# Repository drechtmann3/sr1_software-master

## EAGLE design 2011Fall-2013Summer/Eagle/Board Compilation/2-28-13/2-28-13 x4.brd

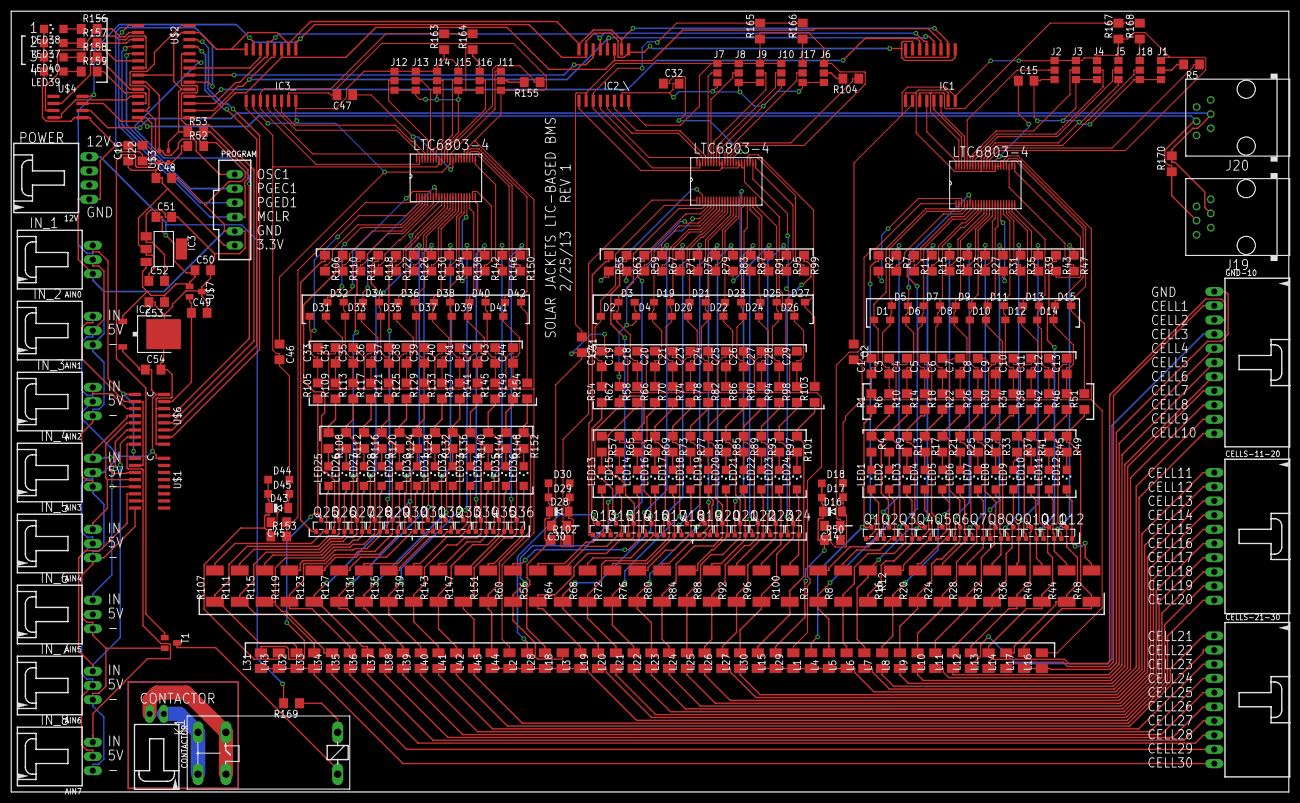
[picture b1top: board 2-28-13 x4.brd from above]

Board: 2 copper layers, 228.6 x 139.7 mm, 437 parts (0 on the bottom side), 350 nets.

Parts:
12V: C-GRID-04-70553; 70553-04
AIN0, AIN1, AIN2, AIN3, AIN4, AIN5, AIN6, AIN7: C-GRID-03-70553; 70553-03
C1, C3, C4, C5, C6, C7, C8, C9, C10, C11, C12, C13, C14, C17, C18, C19, C20, C21, C23, C24, C25, C26, C27, C28, C29, C30, C33, C34, C35, C36, C37, C38, C39, C40, C41, C42, C43, C44, C45: 100nF 100V; C1206
C2, C15, C22, C31, C32, C46, C47, C50, C51, C53: 1uF; C1206
C16, C48, C49, C52, C54: .1uF; C1206
CELLS-11-20, CELLS-21-30: C-GRID-10-70553; 70553-10
CONTACTOR: C-GRID-02-70553; 70553-02
D1, D2, D3, D4, D5, D6, D7, D8, D9, D10, D11, D12, D13, D14, D15, D19, D20, D21, D22, D23, D24, D25, D26, D27, D31, D32, D33, D34, D35, D36, D37, D38, D39, D40, D41, D42: PDZ7.5B; SOD323-W
D16, D28, D43: ZMM5265B-7; MINIMELF
D17, D18, D29, D30, D44, D45: BAT46W; SOD123
GND-10: C-GRID-11-70553; 70553-11
IC1, IC2_\, IC3_: ADUM1401; SO16W
IC2: 7805DT; TO252
IC3: REG1117; SOT223
J1: TOS_LTC1; A0R-JMP
J2: A3_LTC1; A0R-JMP
J3: A2_LTC1; A0R-JMP
J4: A1_LTC1; A0R-JMP
J5: A0_LTC1; A0R-JMP
J6: TOS_LTC2; A0R-JMP
J7: A3_LTC2; A0R-JMP
J8: A2_LTC2; A0R-JMP
J9: A1_LTC2; A0R-JMP
J10: A0_LTC2; A0R-JMP
J11: TOS_LTC3; A0R-JMP
J12: A3_LTC3; A0R-JMP
J13: A2_LTC3; A0R-JMP
J14: A1_LTC3; A0R-JMP
J15: A0_LTC3; A0R-JMP
J16: WDTB_LTC3; A0R-JMP
J17: WDTB_LTC2; A0R-JMP
J18: WDTB_LTC1; A0R-JMP
J19, J20: RJ11-2L-B; RJ11-NO_SHIELD
K1: G2REA
L1, L2, L3, L4, L5, L6, L7, L8, L9, L10, L11, L12, L13, L14, L15, L16, L17, L18, L19, L20, L21, L22, L23, L24, L25, L26, L27, L28, L29, L30, L31, L32, L33, L34, L35, L36, L37, L38, L39, L40, L41, L42, L43, L44, L45: IMC1210ER100K; L3225M
LED1, LED2, LED3, LED4, LED5, LED6, LED7, LED8, LED9, LED10, LED11, LED12, LED13, LED14, LED15, LED16, LED17, LED18, LED19, LED20, LED21, LED22, LED23, LED24, LED25, LED26, LED27, LED28, LED29, LED30, LED31, LED32, LED33, LED34, LED35, LED36: BLUE; CHIPLED_1206
LED37, LED40: YELLOW; CHIPLED_1206
LED38: RED; CHIPLED_1206
LED39: GREEN; CHIPLED_1206
LTC1, LTC2, LTC3: LTC6803-4; SSOP44
PROGRAM: C-GRID-06-70543; 70543-06
Q1, Q2, Q3, Q4, Q5, Q6, Q7, Q8, Q9, Q10, Q11, Q12, Q13, Q14, Q15, Q16, Q17, Q18, Q19, Q20, Q21, Q22, Q23, Q24, Q25, Q26, Q27, Q28, Q29, Q30, Q31, Q32, Q33, Q34, Q35, Q36: SI2351DS; MICRO3
R1, R6, R10, R14, R18, R22, R26, R30, R34, R38, R42, R46, R51, R54, R58, R62, R66, R70, R74, R78, R82, R86, R90, R94, R98, R103, R105, R109, R113, R117, R121, R125, R129, R133, R137, R141, R145, R149, R154: 100 1%; R1206
R2, R7, R11, R15, R19, R23, R27, R31, R35, R39, R43, R47, R55, R59, R63, R67, R71, R75, R79, R83, R87, R91, R95, R99, R106, R110, R114, R118, R122, R126, R130, R134, R138, R142, R146, R150: 3.3K; R1206
R3, R8, R12, R16, R20, R24, R28, R32, R36, R40, R44, R48, R56, R60, R64, R68, R72, R76, R80, R84, R88, R92, R96, R100, R107, R111, R115, R119, R123, R127, R131, R135, R139, R143, R147, R151: 33 1W; R2512
R4, R9, R13, R17, R21, R25, R29, R33, R37, R41, R45, R49, R57, R61, R65, R69, R73, R77, R81, R85, R89, R93, R97, R101, R108, R112, R116, R120, R124, R128, R132, R136, R140, R144, R148, R152, R156, R157, R158, R159: 62; R1206
R5, R104, R155, R163, R164, R165, R166, R167, R168: 1M; R1206
R50, R102, R153: 100; R1206
R52: 10k\; R1206
R53: 470; R1206
R169: 1K; R1206
R170: 120; R1206
T1: PMV56XN; SOT23
U$1: SP720APP; SO16
U$2: PIC24HJ128GP-202; SO28W
U$3: ASE
U$4: MAX3440E; SO-08
U$6: MCP-3008; SO16
U$7: MAX6105; SOT23

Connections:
12V: 12V.4, C50.1, C51.1, C53.1, IC2.1, IC3.3, R169.2, U$7.1
+3V3: C16.1, C48.1, C52.1, IC3.2, PROGRAM.6, R52.1, U$2.13, U$2.28, U$3.1, U$3.4
+5V: AIN0.2, AIN1.2, AIN2.2, AIN3.2, AIN4.2, AIN5.2, AIN6.2, AIN7.2, C54.1, IC1.1, IC1.7, IC2.2, IC2_\.1, IC2_\.7, IC3_.1, IC3_.7, U$1.16, U$4.8, U$6.16
AGND: C17.2, C18.2, C19.2, C20.2, C21.2, C23.2, C24.2, C25.2, C26.2, C27.2, C28.2, C29.2, C30.2, C31.2, C32.2, D28.A, D29.A, D30.A, IC2_\.9, IC2_\.15, J6.3, J7.3, J8.3, J9.3, J10.3, J17.3, L29.2, LTC2.P$27, LTC2.P$28, LTC2.P$29, LTC2.P$30, LTC2.P$35, LTC2.P$36
CELL0: GND-10.1, L16.1, L17.1
CELL1: GND-10.2, L14.1
CELL2: GND-10.3, L13.1
CELL3: GND-10.4, L12.1
CELL4: GND-10.5, L11.1
CELL5: GND-10.6, L10.1
CELL6: GND-10.7, L9.1
CELL7: GND-10.8, L8.1
CELL8: GND-10.9, L7.1
CELL9: GND-10.10, L6.1
CELL10: GND-10.11, L1.1, L4.1, L5.1, L15.1, L29.1, L30.1
CELL11: CELLS-11-20.1, L27.1
CELL12: CELLS-11-20.2, L26.1
CELL13: CELLS-11-20.3, L25.1
CELL14: CELLS-11-20.4, L24.1
CELL15: CELLS-11-20.5, L23.1
CELL16: CELLS-11-20.6, L22.1
CELL17: CELLS-11-20.7, L21.1
CELL18: CELLS-11-20.8, L20.1
CELL19: CELLS-11-20.9, L19.1
CELL20: CELLS-11-20.10, L2.1, L3.1, L18.1, L28.1, L44.1, L45.1
CELL21: CELLS-21-30.1, L42.1
CELL22: CELLS-21-30.2, L41.1
CELL23: CELLS-21-30.3, L40.1
CELL24: CELLS-21-30.4, L39.1
CELL25: CELLS-21-30.5, L38.1
CELL26: CELLS-21-30.6, L37.1
CELL27: CELLS-21-30.7, L36.1
CELL28: CELLS-21-30.8, L35.1
CELL29: CELLS-21-30.9, L34.1
CELL30: CELLS-21-30.10, L31.1, L32.1, L33.1, L43.1
GND: C1.2, C2.2, C3.2, C4.2, C5.2, C6.2, C7.2, C8.2, C9.2, C10.2, C11.2, C12.2, C13.2, C14.2, C15.2, D16.A, D17.A, D18.A, IC1.9, IC1.15, J1.3, J2.3, J3.3, J4.3, J5.3, J18.3, L16.2, LTC1.P$27, LTC1.P$28, LTC1.P$29, LTC1.P$30, LTC1.P$35, LTC1.P$36
GNDIO: 12V.1, AIN0.1, AIN1.1, AIN2.1, AIN3.1, AIN4.1, AIN5.1, AIN6.1, AIN7.1, C16.2, C22.2, C48.2, C49.2, C50.2, C51.2, C52.2, C53.2, C54.2, IC1.2, IC1.8, IC2.3, IC2_\.2, IC2_\.8, IC3.1, IC3_.2, IC3_.8, LED37.C, LED38.C, LED39.C, LED40.C, PROGRAM.5, R52.2, R53.1, T1.2, U$1.8, U$2.8, U$2.19, U$2.27, U$3.2, U$4.5, U$6.9, U$6.14, U$7.3
MCLR: PROGRAM.4, R53.2, U$2.1
unnamed: C1.1, D1.C, LTC1.P$2, R1.2
unnamed: L1.2, Q1.3, R1.1
unnamed: LTC1.P$3, R2.2
unnamed: K1.2, T1.3
unnamed: Q1.1, R2.1
unnamed: LED1.A, Q1.2, R3.2
unnamed: LED1.C, R4.2
unnamed: L4.2, Q2.3, R3.1, R4.1, R6.1
unnamed: C3.1, D1.A, D5.C, LTC1.P$4, R6.2
unnamed: J1.2, R5.2
unnamed: LTC1.P$33, R5.1
unnamed: J4.2, LTC1.P$38
unnamed: J3.2, LTC1.P$39
unnamed: J2.2, LTC1.P$40
unnamed: J5.2, LTC1.P$37
unnamed: LTC1.P$5, R7.2
unnamed: Q2.1, R7.1
unnamed: LED2.A, Q2.2, R8.2
unnamed: LED2.C, R9.2
unnamed: L5.2, Q3.3, R8.1, R9.1, R10.1
unnamed: IC1.12, LTC1.P$44
unnamed: C4.1, D5.A, D6.C, LTC1.P$6, R10.2
unnamed: IC1.13, LTC1.P$42
unnamed: IC1.14, LTC1.P$41
unnamed: LTC1.P$7, R11.2
unnamed: Q3.1, R11.1
unnamed: LED3.A, Q3.2, R12.2
unnamed: LED3.C, R13.2
unnamed: L6.2, Q4.3, R12.1, R13.1, R14.1
unnamed: C15.1, LTC1.P$31
unnamed: C5.1, D6.A, D7.C, LTC1.P$8, R14.2
unnamed: C17.1, D2.C, LTC2.P$2, R54.2
unnamed: LTC1.P$9, R15.2
unnamed: Q4.1, R15.1
unnamed: LED4.A, Q4.2, R16.2
unnamed: LED4.C, R17.2
unnamed: L7.2, Q5.3, R16.1, R17.1, R18.1
unnamed: L2.2, Q13.3, R54.1
unnamed: C6.1, D7.A, D8.C, LTC1.P$10, R18.2
unnamed: LTC2.P$3, R55.2
unnamed: Q13.1, R55.1
unnamed: LTC1.P$11, R19.2
unnamed: Q5.1, R19.1
unnamed: LED5.A, Q5.2, R20.2
unnamed: LED5.C, R21.2
unnamed: L8.2, Q6.3, R20.1, R21.1, R22.1
unnamed: C22.1, U$2.20
unnamed: C7.1, D8.A, D9.C, LTC1.P$12, R22.2
unnamed: LED13.A, Q13.2, R56.2
unnamed: LED13.C, R57.2
unnamed: LTC1.P$13, R23.2
unnamed: Q6.1, R23.1
unnamed: LED6.A, Q6.2, R24.2
unnamed: LED6.C, R25.2
unnamed: L9.2, Q7.3, R24.1, R25.1, R26.1
unnamed: L3.2, Q14.3, R56.1, R57.1, R58.1
unnamed: C8.1, D9.A, D10.C, LTC1.P$14, R26.2
unnamed: C18.1, D2.A, D3.C, LTC2.P$4, R58.2
unnamed: LTC2.P$5, R59.2
unnamed: LTC1.P$15, R27.2
unnamed: Q7.1, R27.1
unnamed: LED7.A, Q7.2, R28.2
unnamed: LED7.C, R29.2
unnamed: L10.2, Q8.3, R28.1, R29.1, R30.1
unnamed: Q14.1, R59.1
unnamed: C9.1, D10.A, D11.C, LTC1.P$16, R30.2
unnamed: LED14.A, Q14.2, R60.2
unnamed: LED14.C, R61.2
unnamed: LTC1.P$17, R31.2
unnamed: Q8.1, R31.1
unnamed: LED8.A, Q8.2, R32.2
unnamed: LED8.C, R33.2
unnamed: L11.2, Q9.3, R32.1, R33.1, R34.1
unnamed: L18.2, Q15.3, R60.1, R61.1, R62.1
unnamed: C10.1, D11.A, D12.C, LTC1.P$18, R34.2
unnamed: C19.1, D3.A, D4.C, LTC2.P$6, R62.2
unnamed: LTC2.P$7, R63.2
unnamed: LTC1.P$19, R35.2
unnamed: Q9.1, R35.1
unnamed: LED9.A, Q9.2, R36.2
unnamed: LED9.C, R37.2
unnamed: L12.2, Q10.3, R36.1, R37.1, R38.1
unnamed: Q15.1, R63.1
unnamed: C11.1, D12.A, D13.C, LTC1.P$20, R38.2
unnamed: LED15.A, Q15.2, R64.2
unnamed: LED15.C, R65.2
unnamed: LTC1.P$21, R39.2
unnamed: Q10.1, R39.1
unnamed: LED10.A, Q10.2, R40.2
unnamed: LED10.C, R41.2
unnamed: L13.2, Q11.3, R40.1, R41.1, R42.1
unnamed: L19.2, Q16.3, R64.1, R65.1, R66.1
unnamed: C12.1, D13.A, D14.C, LTC1.P$22, R42.2
unnamed: C20.1, D4.A, D19.C, LTC2.P$8, R66.2
unnamed: LTC2.P$9, R67.2
unnamed: LTC1.P$23, R43.2
unnamed: Q11.1, R43.1
unnamed: LED11.A, Q11.2, R44.2
unnamed: LED11.C, R45.2
unnamed: L14.2, Q12.3, R44.1, R45.1, R46.1
unnamed: Q16.1, R67.1
unnamed: C13.1, D14.A, D15.C, LTC1.P$24, R46.2
unnamed: LED16.A, Q16.2, R68.2
unnamed: LED16.C, R69.2
unnamed: LTC1.P$25, R47.2
unnamed: Q12.1, R47.1
unnamed: LED12.A, Q12.2, R48.2
unnamed: LED12.C, R49.2
unnamed: L17.2, R48.1, R49.1, R51.1
unnamed: L20.2, Q17.3, R68.1, R69.1, R70.1
unnamed: D15.A, LTC1.P$26, R51.2
unnamed: C21.1, D19.A, D20.C, LTC2.P$10, R70.2
unnamed: D16.C, D17.C, D18.C, L15.2, R50.1
unnamed: C14.1, LTC1.P$1, R50.2
unnamed: LTC2.P$11, R71.2
unnamed: Q17.1, R71.1
unnamed: LED17.A, Q17.2, R72.2
unnamed: LED17.C, R73.2
unnamed: L21.2, Q18.3, R72.1, R73.1, R74.1
unnamed: C23.1, D20.A, D21.C, LTC2.P$12, R74.2
unnamed: LTC2.P$13, R75.2
unnamed: Q18.1, R75.1
unnamed: LED18.A, Q18.2, R76.2
unnamed: LED18.C, R77.2
unnamed: L22.2, Q19.3, R76.1, R77.1, R78.1
unnamed: C24.1, D21.A, D22.C, LTC2.P$14, R78.2
unnamed: LTC2.P$15, R79.2
unnamed: Q19.1, R79.1
unnamed: LED19.A, Q19.2, R80.2
unnamed: LED19.C, R81.2
unnamed: L23.2, Q20.3, R80.1, R81.1, R82.1
unnamed: C25.1, D22.A, D23.C, LTC2.P$16, R82.2
unnamed: LTC2.P$17, R83.2
unnamed: Q20.1, R83.1
unnamed: LED20.A, Q20.2, R84.2
unnamed: LED20.C, R85.2
unnamed: L24.2, Q21.3, R84.1, R85.1, R86.1
unnamed: C26.1, D23.A, D24.C, LTC2.P$18, R86.2
unnamed: LTC2.P$19, R87.2
unnamed: Q21.1, R87.1
unnamed: LED21.A, Q21.2, R88.2
unnamed: LED21.C, R89.2
unnamed: L25.2, Q22.3, R88.1, R89.1, R90.1
unnamed: C27.1, D24.A, D25.C, LTC2.P$20, R90.2
unnamed: LTC2.P$21, R91.2
unnamed: Q22.1, R91.1
unnamed: LED22.A, Q22.2, R92.2
unnamed: LED22.C, R93.2
unnamed: L26.2, Q23.3, R92.1, R93.1, R94.1
unnamed: C28.1, D25.A, D26.C, LTC2.P$22, R94.2
unnamed: LTC2.P$23, R95.2
unnamed: Q23.1, R95.1
unnamed: LED23.A, Q23.2, R96.2
unnamed: LED23.C, R97.2
unnamed: L27.2, Q24.3, R96.1, R97.1, R98.1
unnamed: C29.1, D26.A, D27.C, LTC2.P$24, R98.2
unnamed: LTC2.P$25, R99.2
unnamed: Q24.1, R99.1
unnamed: LED24.A, Q24.2, R100.2
unnamed: LED24.C, R101.2
unnamed: L30.2, R100.1, R101.1, R103.1
unnamed: D27.A, LTC2.P$26, R103.2
unnamed: D28.C, D29.C, D30.C, L28.2, R102.1
unnamed: C30.1, LTC2.P$1, R102.2
unnamed: J6.2, R104.2
unnamed: LTC2.P$33, R104.1
unnamed: J8.2, LTC2.P$39
unnamed: J7.2, LTC2.P$40
unnamed: J9.2, LTC2.P$38
unnamed: J10.2, LTC2.P$37
unnamed: K1.1, R169.1
unnamed: IC2_\.12, LTC2.P$44
unnamed: IC2_\.13, LTC2.P$42
unnamed: IC2_\.14, LTC2.P$41
unnamed: C32.1, LTC2.P$31
unnamed: C33.1, D31.C, LTC3.P$2, R105.2
unnamed: L31.2, Q25.3, R105.1
unnamed: LTC3.P$3, R106.2
unnamed: Q25.1, R106.1
unnamed: LED25.A, Q25.2, R107.2
unnamed: LED25.C, R108.2
unnamed: L32.2, Q26.3, R107.1, R108.1, R109.1
unnamed: C34.1, D31.A, D32.C, LTC3.P$4, R109.2
unnamed: LTC3.P$5, R110.2
unnamed: Q26.1, R110.1
unnamed: LED26.A, Q26.2, R111.2
unnamed: LED26.C, R112.2
unnamed: L33.2, Q27.3, R111.1, R112.1, R113.1
unnamed: C35.1, D32.A, D33.C, LTC3.P$6, R113.2
unnamed: LTC3.P$7, R114.2
unnamed: Q27.1, R114.1
unnamed: LED27.A, Q27.2, R115.2
unnamed: LED27.C, R116.2
unnamed: L34.2, Q28.3, R115.1, R116.1, R117.1
unnamed: C36.1, D33.A, D34.C, LTC3.P$8, R117.2
unnamed: LTC3.P$9, R118.2
unnamed: Q28.1, R118.1
unnamed: LED28.A, Q28.2, R119.2
unnamed: LED28.C, R120.2
unnamed: L35.2, Q29.3, R119.1, R120.1, R121.1
unnamed: C37.1, D34.A, D35.C, LTC3.P$10, R121.2
unnamed: LTC3.P$11, R122.2
unnamed: Q29.1, R122.1
unnamed: LED29.A, Q29.2, R123.2
unnamed: LED29.C, R124.2
unnamed: L36.2, Q30.3, R123.1, R124.1, R125.1
unnamed: C38.1, D35.A, D36.C, LTC3.P$12, R125.2
unnamed: LTC3.P$13, R126.2
unnamed: Q30.1, R126.1
unnamed: LED30.A, Q30.2, R127.2
unnamed: LED30.C, R128.2
unnamed: L37.2, Q31.3, R127.1, R128.1, R129.1
unnamed: C39.1, D36.A, D37.C, LTC3.P$14, R129.2
unnamed: LTC3.P$15, R130.2
unnamed: Q31.1, R130.1
unnamed: LED31.A, Q31.2, R131.2
unnamed: LED31.C, R132.2
unnamed: L38.2, Q32.3, R131.1, R132.1, R133.1
unnamed: C40.1, D37.A, D38.C, LTC3.P$16, R133.2
unnamed: LTC3.P$17, R134.2
unnamed: Q32.1, R134.1
unnamed: LED32.A, Q32.2, R135.2
unnamed: LED32.C, R136.2
unnamed: L39.2, Q33.3, R135.1, R136.1, R137.1
unnamed: C41.1, D38.A, D39.C, LTC3.P$18, R137.2
unnamed: LTC3.P$19, R138.2
unnamed: Q33.1, R138.1
unnamed: LED33.A, Q33.2, R139.2
unnamed: LED33.C, R140.2
unnamed: L40.2, Q34.3, R139.1, R140.1, R141.1
unnamed: C42.1, D39.A, D40.C, LTC3.P$20, R141.2
unnamed: LTC3.P$21, R142.2
unnamed: Q34.1, R142.1
unnamed: LED34.A, Q34.2, R143.2
unnamed: LED34.C, R144.2
unnamed: L41.2, Q35.3, R143.1, R144.1, R145.1
unnamed: C43.1, D40.A, D41.C, LTC3.P$22, R145.2
unnamed: LTC3.P$23, R146.2
unnamed: Q35.1, R146.1
unnamed: LED35.A, Q35.2, R147.2
unnamed: LED35.C, R148.2
unnamed: L42.2, Q36.3, R147.1, R148.1, R149.1
unnamed: C44.1, D41.A, D42.C, LTC3.P$24, R149.2
unnamed: LTC3.P$25, R150.2
unnamed: Q36.1, R150.1
unnamed: LED36.A, Q36.2, R151.2
unnamed: LED36.C, R152.2
unnamed: L45.2, R151.1, R152.1, R154.1
unnamed: D42.A, LTC3.P$26, R154.2
unnamed: D43.C, D44.C, D45.C, L43.2, R153.1
unnamed: C45.1, LTC3.P$1, R153.2
unnamed: J11.2, R155.2
unnamed: LTC3.P$33, R155.1
unnamed: J13.2, LTC3.P$39
unnamed: J12.2, LTC3.P$40
unnamed: J14.2, LTC3.P$38
unnamed: J15.2, LTC3.P$37
unnamed: IC3_.12, LTC3.P$44
unnamed: IC3_.13, LTC3.P$42
unnamed: IC3_.14, LTC3.P$41
unnamed: C47.1, LTC3.P$31
unnamed: AIN7.3, U$1.7, U$6.8
unnamed: AIN6.3, U$1.6, U$6.7
unnamed: AIN5.3, U$1.5, U$6.6
unnamed: AIN0.3, U$1.1, U$6.1
unnamed: AIN1.3, U$1.2, U$6.2
unnamed: AIN2.3, U$6.3
unnamed: AIN3.3, U$1.3, U$6.4
unnamed: AIN4.3, U$1.4, U$6.5
unnamed: LED37.A, R157.1
unnamed: LED38.A, R156.1
unnamed: LED39.A, R159.1
unnamed: LED40.A, R158.1
unnamed: CONTACTOR.2, K1.P, K1.P@
unnamed: CONTACTOR.1, K1.S, K1.S@
unnamed: IC1.11, LTC1.P$43, R167.2, R168.2
unnamed: J18.1, R168.1
unnamed: J18.2, LTC1.P$34
unnamed: IC2_\.11, LTC2.P$43, R165.2, R166.2
unnamed: J17.1, R166.1
unnamed: J17.2, LTC2.P$34
unnamed: J16.2, LTC3.P$34
unnamed: IC3_.11, LTC3.P$43, R163.2, R164.2
unnamed: J16.1, R164.1
unnamed: J19.3, J20.3, R170.1, U$4.7
unnamed: J19.4, J20.4, R170.2, U$4.6
OSC1: PROGRAM.1, U$2.9, U$3.3
PE: C33.2, C34.2, C35.2, C36.2, C37.2, C38.2, C39.2, C40.2, C41.2, C42.2, C43.2, C44.2, C45.2, C46.2, C47.2, D43.A, D44.A, D45.A, IC3_.9, IC3_.15, J11.3, J12.3, J13.3, J14.3, J15.3, J16.3, L44.2, LTC3.P$27, LTC3.P$28, LTC3.P$29, LTC3.P$30, LTC3.P$35, LTC3.P$36
PGEC1: PROGRAM.2, U$2.5
PGED1: PROGRAM.3, U$2.4
RA0: R156.2, U$2.2
RA1: R157.2, U$2.3
RA3: R158.2, U$2.10
RA4: R159.2, U$2.12
RB2: U$2.6, U$4.2
RB3: U$2.7, U$4.3
RB4: U$2.11, U$4.4
RB5: T1.1, U$2.14
RB6: IC1.3, IC2_\.3, IC3_.3, U$2.15
RB7: IC1.4, IC2_\.4, IC3_.4, U$2.16
RB8: IC1.5, IC2_\.5, IC3_.5, U$2.17
RB9: IC1.6, U$2.18
RB10: IC2_\.6, U$2.21
RB11: IC3_.6, U$2.22
RB12: U$2.23, U$6.13
RB13: U$2.24, U$6.12
RB14: U$2.25, U$6.11
RB15: U$2.26, U$6.10
V+: C2.1, IC1.10, IC1.16, J1.1, J2.1, J3.1, J4.1, J5.1, LTC1.P$32, R167.1
VCC: C31.1, IC2_\.10, IC2_\.16, J6.1, J7.1, J8.1, J9.1, J10.1, LTC2.P$32, R165.1
VCC/2: C46.1, IC3_.10, IC3_.16, J11.1, J12.1, J13.1, J14.1, J15.1, LTC3.P$32, R163.1
VCCIO: C49.1, U$6.15, U$7.2

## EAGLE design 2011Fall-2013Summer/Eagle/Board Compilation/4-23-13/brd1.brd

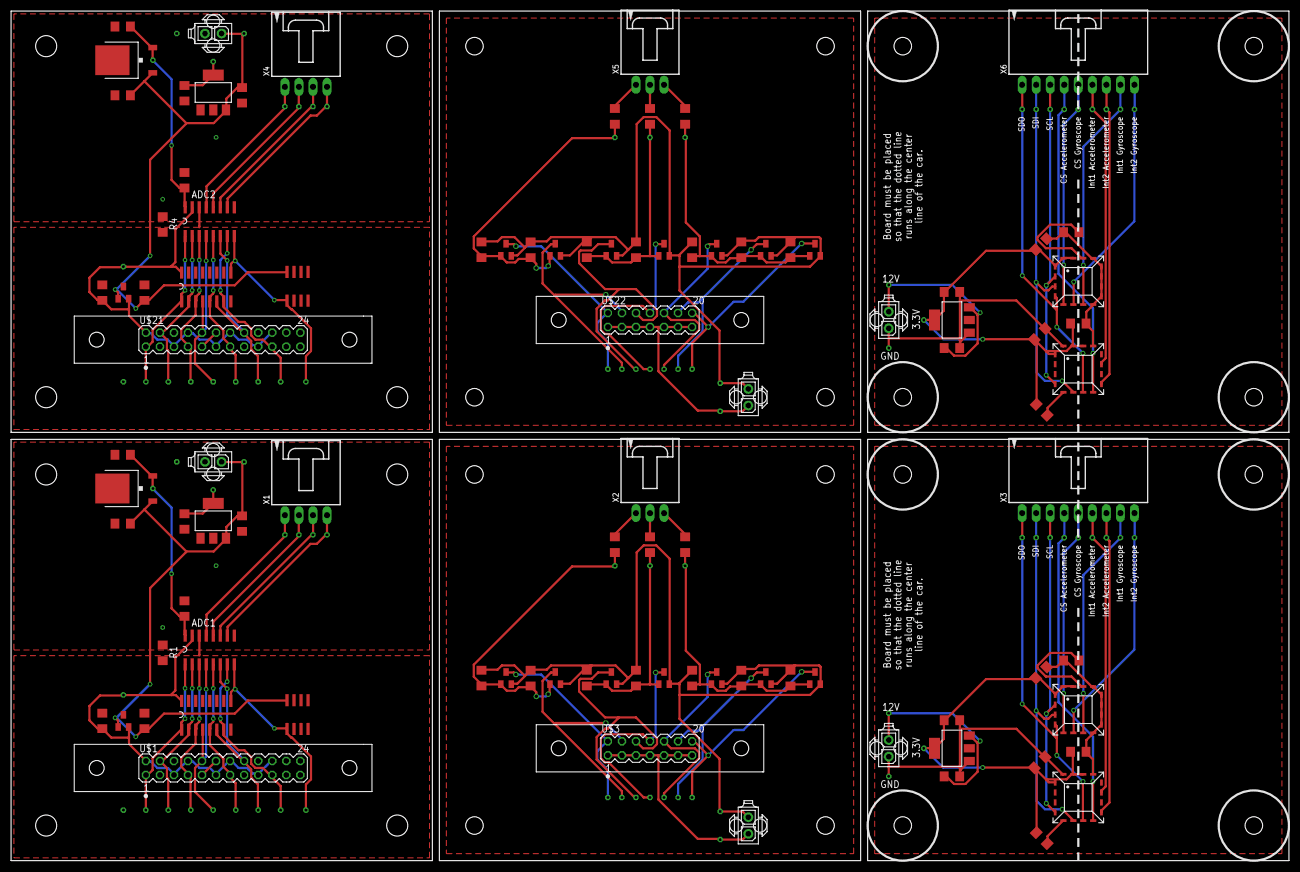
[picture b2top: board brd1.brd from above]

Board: 2 copper layers, 231.1 x 153.7 mm, 182 parts (0 on the bottom side), 92 nets.

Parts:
3.3V_TP, 3.3V_TP1, 5V_TP, 5V_TP1, 12V, 12V1, 12V2, 12V3: TESTPAD-20MIL; 20MIL
5V, 5V1: LM7805TV; TO252
5VREF, 5VREF1: MAX6105; SOT23
317CAP1, 317CAP2, 317CAP3, 317CAP4, 6103CAP1, 6103CAP2, 6103CAP3, 6103CAP4, 7805CAP2, 7805CAP3: 1uF; C1206
7805CAP1, 7805CAP4: .33uF; C1206
ADC1, ADC2: MCP-3008; SO16
ADC_CAP1, ADC_CAP2: .1uF; C1206
AGND, AGND1: TESTPAD-20MIL; 20MIL
B, B1: TESTPAD-20MIL; 20MIL
BC, BC1: TESTPAD-20MIL; 20MIL
BL, BL1: TESTPAD-20MIL; 20MIL
BLC, BLC1: TESTPAD-20MIL; 20MIL
BLINKER-L1, BLINKER-L2, BLINKER-L3, BLINKER-L4: PMV56XN215; SOT23
BLINKER-R1, BLINKER-R2, BLINKER-R3, BLINKER-R4: PMV56XN215; SOT23
BLLB, BLLB1: TESTPAD-20MIL; 20MIL
BLLF, BLLF1: TESTPAD-20MIL; 20MIL
BLRB, BLRB1: TESTPAD-20MIL; 20MIL
BLRF, BLRF1: TESTPAD-20MIL; 20MIL
BR, BR1: TESTPAD-20MIL; 20MIL
BRAKE-C1, BRAKE-C2: N-CHANNEL_MOSFETPMV56XN,215; SOT23
BRAKE-L1, BRAKE-L2: PMV56XN215; SOT23
BRAKE-R1, BRAKE-R2: PMV56XN215; SOT23
BRC, BRC1: TESTPAD-20MIL; 20MIL
C1, C2, C6, C7: 1uF; C1206
C1_1, C1_20: 10nF 25V; C1206
C2_1, C2_20, C4_1, C4_331: 10uF; C1206
C3_1, C3_20, C5_1, C5_331: 100nF; C1206
GND, GND1, GND2, GND3: TESTPAD-20MIL; 20MIL
IC1, IC3: LD117AS12TR; SOT223
IC2, IC4: LD117AS18TR; SOT223
IN1, IN2, IN3, IN4, IN5, IN6, IN7, IN8, IN9, IN10, IN11, IN12, IN13, IN14, IN15, IN16: TESTPAD-20MIL; 20MIL
J1, J2, J3, J4, J5, J6: 794681-2
R1, R4: 0; R1206
R2, R3, R5, R6, R7, R8, R9, R10, R11, R12, R13, R14, R15, R16, R17, R18, R19, R20, R21, R22: 1k; R1206
SPI_CLK, SPI_CLK1: TESTPAD-20MIL; 20MIL
SPI_CS1, SPI_CS2: TESTPAD-20MIL; 20MIL
SPI_DIN, SPI_DIN1: TESTPAD-20MIL; 20MIL
SPI_DOUT, SPI_DOUT1: TESTPAD-20MIL; 20MIL
U$1, U$21: AMP_LATCH_22; MA22-2
U$2, U$20: LM35; SO-08
U$3, U$22: AMP_LATCH_14; MA14-2
U$4, U$23: L3GD20; LGA16
U$5, U$24: LIS331HH; LGA16
U$6, U$19: SP720APP; SO16
U$7, U$8, U$9, U$10, U$11, U$12, U$13, U$14, U$15, U$16, U$17, U$18, U$25, U$26, U$27, U$28, U$29, U$30, U$31, U$32, U$33, U$34, U$35, U$36: TESTPAD-20MIL; 20MIL
VREF_TP, VREF_TP1: TESTPAD-20MIL; 20MIL
X1, X4: C-GRID-04-70553; 70553-04
X2, X5: C-GRID-03-70553; 70553-03
X3, X6: C-GRID-09-70553; 70553-09

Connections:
3.3V: 3.3V_TP.P$1, 317CAP2.1, IC1.4
3.3V1: C2_20.2, C3_20.2, C4_331.2, C5_331.2, C7.1, IC2.4, U$4.1, U$4.15, U$4.16, U$5.1, U$5.14, U$5.15, U$18.P$1
3.3V2: 3.3V_TP1.P$1, 317CAP4.1, IC3.4
3.3V3: C2.1, C2_1.2, C3_1.2, C4_1.2, C5_1.2, IC4.4, U$23.1, U$23.15, U$23.16, U$24.1, U$24.14, U$24.15, U$36.P$1
5V: 5V.2, 5V_TP.P$1, 7805CAP2.1, ADC1.16, ADC_CAP1.1
5V1: 5V1.2, 5V_TP1.P$1, 7805CAP3.1, ADC2.16, ADC_CAP2.1
12V: 5V.1, 5VREF.1, 12V.P$1, 317CAP1.1, 6103CAP1.1, 7805CAP1.1, IC1.3, J1.1, U$2.8
12V1: 12V1.P$1, J2.1, U$3.1, U$3.3, U$3.5, U$3.7, U$3.9, U$3.11, U$3.13
12V2: C6.1, IC2.3, J3.2, U$16.P$1
12V3: 5V1.1, 5VREF1.1, 12V2.P$1, 317CAP3.1, 6103CAP3.1, 7805CAP4.1, IC3.3, J4.1, U$20.8
12V4: 12V3.P$1, J5.1, U$22.1, U$22.3, U$22.5, U$22.7, U$22.9, U$22.11, U$22.13
12V5: C1.1, IC4.3, J6.2, U$34.P$1
AGND: 5VREF.3, 6103CAP1.2, 6103CAP2.2, ADC1.14, AGND.P$1, R1.2, U$1.3, U$1.6, U$1.9, U$1.12, U$1.15, U$1.18, U$1.21, U$2.4, U$6.8
AGND1: 5VREF1.3, 6103CAP3.2, 6103CAP4.2, ADC2.14, AGND1.P$1, R4.2, U$19.8, U$20.4, U$21.3, U$21.6, U$21.9, U$21.12, U$21.15, U$21.18, U$21.21
BLINKER_L: BLC.P$1, BLINKER-L1.1, BLINKER-L2.1, R5.2, R6.2, R10.2
BLINKER_L1: BLC1.P$1, BLINKER-L3.1, BLINKER-L4.1, R12.2, R13.2, R22.2
BLINKER_L_BACK_-: BLINKER-L2.3, BLLB.P$1, U$3.6
BLINKER_L_BACK_-1: BLINKER-L4.3, BLLB1.P$1, U$22.6
BLINKER_L_FRONT_-: BLINKER-L1.3, BLLF.P$1, U$3.8
BLINKER_L_FRONT_-1: BLINKER-L3.3, BLLF1.P$1, U$22.8
BLINKER_R: BLINKER-R1.1, BLINKER-R2.1, BRC.P$1, R7.1, R14.2, R15.2
BLINKER_R1: BLINKER-R3.1, BLINKER-R4.1, BRC1.P$1, R17.2, R18.2, R20.1
BLINKER_R_BACK_-: BLINKER-R2.3, BLRB.P$1, U$3.2
BLINKER_R_BACK_-1: BLINKER-R4.3, BLRB1.P$1, U$22.2
BLINKER_R_FRONT_-: BLINKER-R1.3, BLRF.P$1, U$3.4
BLINKER_R_FRONT_-1: BLINKER-R3.3, BLRF1.P$1, U$22.4
BRAKE: B.P$1, BRAKE-C1.1, BRAKE-L1.1, BRAKE-R1.1, R2.2, R3.2, R9.2, R16.2
BRAKE1: B1.P$1, BRAKE-C2.1, BRAKE-L2.1, BRAKE-R2.1, R8.2, R11.2, R19.2, R21.2
BRAKE_C_-: BC.P$1, BRAKE-C1.3, U$3.12
BRAKE_C_-1: BC1.P$1, BRAKE-C2.3, U$22.12
BRAKE_L_-: BL.P$1, BRAKE-L1.3, U$3.10
BRAKE_L_-1: BL1.P$1, BRAKE-L2.3, U$22.10
BRAKE_R_-: BR.P$1, BRAKE-R1.3, U$3.14
BRAKE_R_-1: BR1.P$1, BRAKE-R2.3, U$22.14
CS_ACCEL: U$5.8, U$10.P$1, X3.4
CS_ACCEL1: U$24.8, U$28.P$1, X6.4
CS_GYRO: U$4.5, U$11.P$1, X3.5
CS_GYRO1: U$23.5, U$29.P$1, X6.5
GND: 5V.3, 317CAP1.2, 317CAP2.2, 7805CAP1.2, 7805CAP2.2, ADC1.9, ADC_CAP1.2, GND.P$1, IC1.1, J1.2, R1.1
GND1: BLINKER-L1.2, BLINKER-L2.2, BLINKER-R1.2, BLINKER-R2.2, BRAKE-C1.2, BRAKE-L1.2, BRAKE-R1.2, GND1.P$1, J2.2, R2.1, R3.1, R5.1, R6.1, R14.1, R15.1, R16.1
GND2: C1_20.1, C2_20.1, C3_20.1, C4_331.1, C5_331.1, C6.2, C7.2, IC2.1, J3.1, U$4.8, U$4.9, U$4.10, U$4.11, U$4.12, U$4.13, U$5.5, U$5.10, U$5.12, U$5.13, U$5.16, U$17.P$1
GND3: 5V1.3, 317CAP3.2, 317CAP4.2, 7805CAP3.2, 7805CAP4.2, ADC2.9, ADC_CAP2.2, GND2.P$1, IC3.1, J4.2, R4.1
GND4: BLINKER-L3.2, BLINKER-L4.2, BLINKER-R3.2, BLINKER-R4.2, BRAKE-C2.2, BRAKE-L2.2, BRAKE-R2.2, GND3.P$1, J5.2, R8.1, R11.1, R12.1, R13.1, R17.1, R18.1, R19.1
GND5: C1.2, C1_1.1, C2.2, C2_1.1, C3_1.1, C4_1.1, C5_1.1, IC4.1, J6.1, U$23.8, U$23.9, U$23.10, U$23.11, U$23.12, U$23.13, U$24.5, U$24.10, U$24.12, U$24.13, U$24.16, U$35.P$1
IN1: ADC1.1, IN1.P$1, U$1.1, U$6.1
IN2: ADC1.2, IN2.P$1, U$1.4, U$6.2
IN3: ADC1.3, IN3.P$1, U$1.7, U$6.3
IN4: ADC1.4, IN4.P$1, U$1.10, U$6.4
IN5: ADC1.5, IN5.P$1, U$1.13, U$6.5
IN6: ADC1.6, IN6.P$1, U$1.16, U$6.6
IN7: ADC1.7, IN7.P$1, U$1.19, U$6.7
IN8: ADC1.8, IN8.P$1, U$2.1, U$6.9
IN9: ADC2.1, IN9.P$1, U$19.1, U$21.1
IN10: ADC2.2, IN10.P$1, U$19.2, U$21.4
IN11: ADC2.3, IN11.P$1, U$19.3, U$21.7
IN12: ADC2.4, IN12.P$1, U$19.4, U$21.10
IN13: ADC2.8, IN16.P$1, U$19.9, U$20.1
IN14: ADC2.7, IN15.P$1, U$19.7, U$21.19
IN15: ADC2.6, IN14.P$1, U$19.6, U$21.16
IN16: ADC2.5, IN13.P$1, U$19.5, U$21.13
INT1_ACCEL: U$5.11, U$12.P$1, X3.6
INT1_ACCEL1: U$24.11, U$30.P$1, X6.6
INT1_GYRO: U$4.7, U$14.P$1, X3.8
INT1_GYRO1: U$23.7, U$32.P$1, X6.8
INT2_ACCEL: U$5.9, U$13.P$1, X3.7
INT2_ACCEL1: U$24.9, U$31.P$1, X6.7
INT2_GYRO: U$4.6, U$15.P$1, X3.9
INT2_GYRO1: U$23.6, U$33.P$1, X6.9
unnamed: R7.2, X2.1
unnamed: R10.1, X2.2
unnamed: R9.1, X2.3
unnamed: C1_20.2, U$4.14
unnamed: R20.2, X5.1
unnamed: R22.1, X5.2
unnamed: R21.1, X5.3
unnamed: C1_1.2, U$23.14
SCL: U$4.2, U$5.4, U$9.P$1, X3.3
SCL1: U$23.2, U$24.4, U$27.P$1, X6.3
SDI: U$4.3, U$5.6, U$8.P$1, X3.2
SDI1: U$23.3, U$24.6, U$26.P$1, X6.2
SDO: U$4.4, U$5.7, U$7.P$1, X3.1
SDO1: U$23.4, U$24.7, U$25.P$1, X6.1
SPI_CLK: ADC1.13, SPI_CLK.P$1, X1.1
SPI_CLK1: ADC2.13, SPI_CLK1.P$1, X4.1
SPI_CS1: ADC1.10, SPI_CS1.P$1, X1.4
SPI_CS2: ADC2.10, SPI_CS2.P$1, X4.4
SPI_DIN: ADC1.11, SPI_DIN.P$1, X1.3
SPI_DIN1: ADC2.11, SPI_DIN1.P$1, X4.3
SPI_DOUT: ADC1.12, SPI_DOUT.P$1, X1.2
SPI_DOUT1: ADC2.12, SPI_DOUT1.P$1, X4.2
VREF: 5VREF.2, 6103CAP2.1, ADC1.15, U$1.2, U$1.5, U$1.8, U$1.11, U$1.14, U$1.17, U$1.20, U$6.16, VREF_TP.P$1
VREF1: 5VREF1.2, 6103CAP4.1, ADC2.15, U$19.16, U$21.2, U$21.5, U$21.8, U$21.11, U$21.14, U$21.17, U$21.20, VREF_TP1.P$1

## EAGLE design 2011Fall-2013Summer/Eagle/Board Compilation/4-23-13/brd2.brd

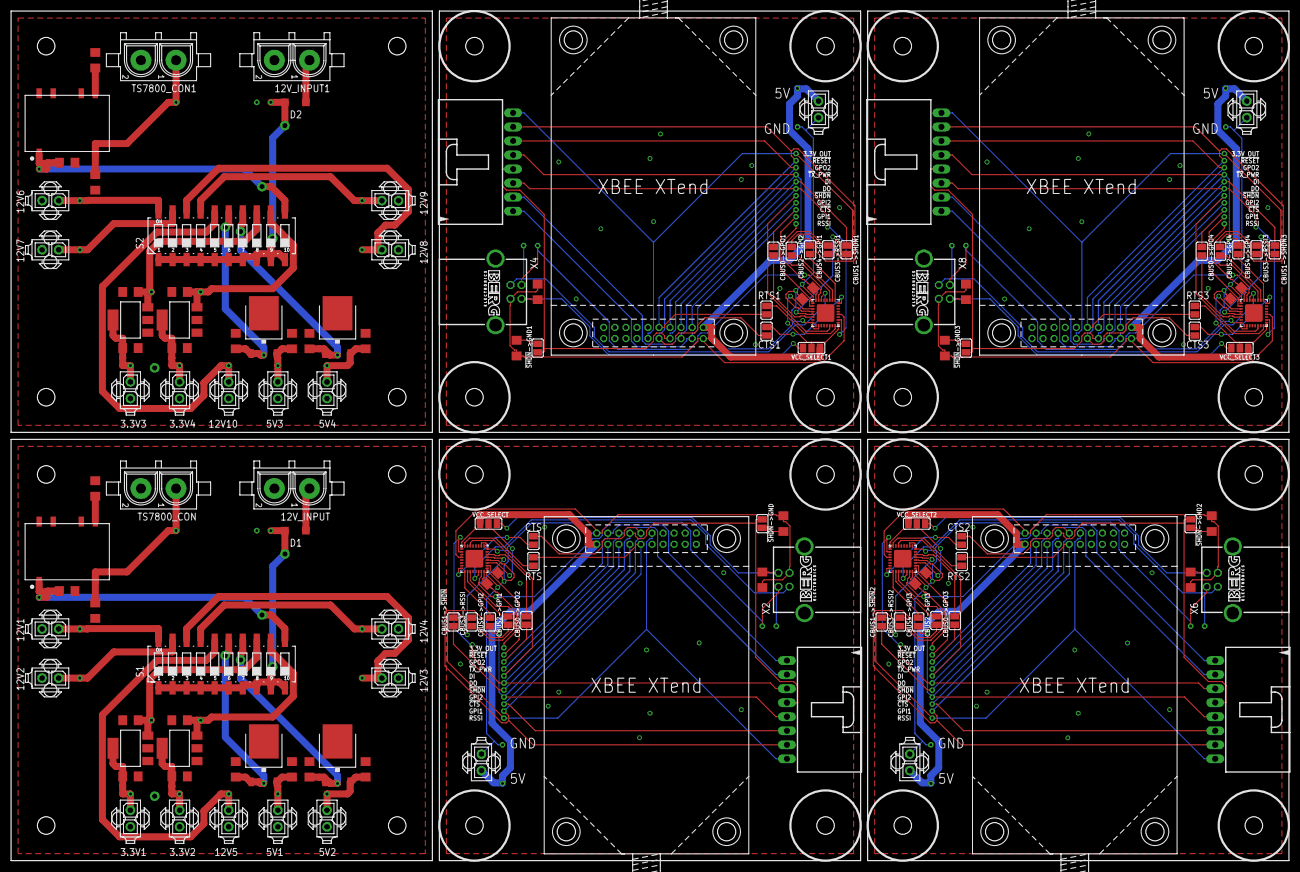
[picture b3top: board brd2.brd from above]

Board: 2 copper layers, 231.1 x 153.7 mm, 220 parts (0 on the bottom side), 138 nets.

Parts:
3.3V1, 3.3V2, 3.3V3, 3.3V4, 5V1, 5V2, 5V3, 5V4, 12V1, 12V2, 12V3, 12V4, 12V5, 12V6, 12V7, 12V8, 12V9, 12V10: 794681-2
3.3V_OUT, 3.3V_OUT1, 3.3V_OUT2, 3.3V_OUT3: TESTPAD-20MIL; 20MIL
12V_INPUT, 12V_INPUT1: 350759-4
317CAP1, 317CAP3, 317CAP4, 317CAP9: .33uF; C1206
317CAP2, 317CAP5, 317CAP8, 317CAP10: 1uF; C1206
!RESET!, !RESET!1, !RESET!2, !RESET!3: TESTPAD-20MIL; 20MIL
!SHDN!->GND, !SHDN!->GND1, !SHDN!->GND2, !SHDN!->GND3: !SHDN!-GND; SJ
C1, C2, C3, C4, C7, C8, C9, C10: 1uF; C1206
C5, C6, C11, C12, C13, C14, C15, C16: 100nF; C1206
CBUS0->GPO1, CBUS0->GPO2, CBUS0->GPO3, CBUS0->GPO4, CBUS1->!SHDN!, CBUS1->!SHDN!1, CBUS1->!SHDN!2, CBUS1->!SHDN!3, CBUS2->GPI1, CBUS2->GPI2, CBUS2->GPI3, CBUS2->GPI4, CBUS3->RSSI, CBUS3->RSSI1, CBUS3->RSSI2, CBUS3->RSSI3, CBUS4->GPI1, CBUS4->GPI2, CBUS4->GPI3, CBUS4->GPI4: SJ
CTS, CTS1, CTS2, CTS3: SJ
D1, D2: SOD123
IC1, IC6, IC7, IC8: FT232RQ; QFN32
IC2, IC3, IC4, IC5: LD117AS12TR; SOT223
J1, J2, J3, J4: 794681-2
PWR_1, PWR_2, PWR_3, PWR_4: 7805DT; TO252
R1, R2, R3, R4: 10K; R1206
RTS, RTS1, RTS2, RTS3: SJ
S1, S2: 219-10; CTS-219-10
TS7800_CON, TS7800_CON1: 350759-4
U$1, U$3, U$4, U$5, U$6, U$7, U$8, U$9, U$10, U$11, U$12, U$13, U$14, U$15, U$16, U$17, U$18, U$20, U$21, U$22, U$23, U$24, U$25, U$26, U$27, U$28, U$29, U$30, U$31, U$32, U$34, U$35, U$36, U$37, U$38, U$39, U$40, U$41, U$42, U$43, U$44, U$45, U$46, U$47, U$48, U$49, U$50, U$52, U$53, U$54, U$55, U$56, U$57, U$58, U$59, U$60, U$61, U$62, U$63, U$64, U$66, U$67, U$68, U$69, U$70, U$71, U$72, U$73, U$74, U$75, U$76, U$77, U$78, U$80, U$81, U$82, U$83, U$84, U$85, U$86, U$87, U$88, U$89, U$90, U$91, U$92: TESTPAD-20MIL; 20MIL
U$2, U$33: V7805
U$19, U$51, U$65, U$79: XTEND
V7805_C1, V7805_C2, V7805_C3, V7805_C4, V7805_C5, V7805_C6: 1uF; C1206
VCC_SELECT, VCC_SELECT1, VCC_SELECT2, VCC_SELECT3: SJ_2
X1, X3, X5, X7: C-GRID-08-70553; 70553-08
X2, X4, X6, X8: PN61729-S

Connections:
3.3V1: 3.3V1.1, 317CAP8.1, IC3.4, U$14.P$1
3.3V1_EN: 317CAP3.1, IC3.3, S1.13, U$6.P$1
3.3V1_EN1: 317CAP1.1, IC5.3, S2.13, U$38.P$1
3.3V2: 3.3V2.1, 317CAP10.1, IC2.4, U$15.P$1
3.3V2_EN: 317CAP9.1, IC2.3, S1.12, U$5.P$1
3.3V2_EN1: 317CAP4.1, IC4.3, S2.12, U$37.P$1
3.3V3: 3.3V3.1, 317CAP2.1, IC5.4, U$46.P$1
3.3V4: 3.3V4.1, 317CAP5.1, IC4.4, U$47.P$1
5V1: 5V1.1, C2.1, PWR_1.2, U$1.P$1
5V1_EN: C1.1, PWR_1.1, S1.15, U$8.P$1
5V1_EN1: C7.1, PWR_3.1, S2.15, U$40.P$1
5V2: 5V2.1, C4.1, PWR_2.2, U$3.P$1
5V2_EN: C3.1, PWR_2.1, S1.14, U$7.P$1
5V2_EN1: C9.1, PWR_4.1, S2.14, U$39.P$1
5V3: 5V4.1, C10.1, PWR_4.2, U$35.P$1
5V4: 5V3.1, C8.1, PWR_3.2, U$34.P$1
12V: D1.C, S1.1, S1.2, S1.3, S1.4, S1.5, S1.6, S1.7, S1.8, S1.9, S1.10, U$17.P$1
12V1: D2.C, S2.1, S2.2, S2.3, S2.4, S2.5, S2.6, S2.7, S2.8, S2.9, S2.10, U$49.P$1
12V1_EN: 12V1.1, S1.20, U$13.P$1
12V1_EN1: 12V6.1, S2.20, U$45.P$1
12V2_EN: 12V2.1, S1.19, U$12.P$1
12V2_EN1: 12V7.1, S2.19, U$44.P$1
12V3_EN: 12V3.1, S1.18, U$11.P$1
12V3_EN1: 12V8.1, S2.18, U$43.P$1
12V4_EN: 12V4.1, S1.17, U$10.P$1
12V4_EN1: 12V9.1, S2.17, U$42.P$1
12V5_EN: 12V5.1, S1.16, U$9.P$1
12V5_EN1: 12V10.1, S2.16, U$41.P$1
CTS: CTS.2, U$19.9, U$24.P$1, X1.6
CTS1: CTS1.2, U$51.9, U$56.P$1, X3.6
CTS2: CTS2.2, U$65.9, U$70.P$1, X5.6
CTS3: CTS3.2, U$79.9, U$84.P$1, X7.6
GND: 3.3V1.2, 3.3V2.2, 5V1.2, 5V2.2, 12V1.2, 12V2.2, 12V3.2, 12V4.2, 12V5.2, 12V_INPUT.2, 317CAP3.2, 317CAP8.2, 317CAP9.2, 317CAP10.2, C1.2, C2.2, C3.2, C4.2, IC2.1, IC3.1, PWR_1.3, PWR_2.3, TS7800_CON.2, U$2.7, U$2.9, U$18.P$1, V7805_C4.2, V7805_C5.2, V7805_C6.2
GND1: C5.1, C6.2, IC1.4, IC1.17, IC1.20, IC1.24, IC1.26, J1.2, R1.2, U$19.1, U$20.P$1, X2.4
GND2: 3.3V3.2, 3.3V4.2, 5V3.2, 5V4.2, 12V6.2, 12V7.2, 12V8.2, 12V9.2, 12V10.2, 12V_INPUT1.2, 317CAP1.2, 317CAP2.2, 317CAP4.2, 317CAP5.2, C7.2, C8.2, C9.2, C10.2, IC4.1, IC5.1, PWR_3.3, PWR_4.3, TS7800_CON1.2, U$33.7, U$33.9, U$50.P$1, V7805_C1.2, V7805_C2.2, V7805_C3.2
GND3: C11.1, C12.2, IC6.4, IC6.17, IC6.20, IC6.24, IC6.26, J2.2, R2.2, U$51.1, U$52.P$1, X4.4
GND4: C13.1, C14.2, IC7.4, IC7.17, IC7.20, IC7.24, IC7.26, J3.2, R3.2, U$65.1, U$66.P$1, X6.4
GND5: C15.1, C16.2, IC8.4, IC8.17, IC8.20, IC8.24, IC8.26, J4.2, R4.2, U$79.1, U$80.P$1, X8.4
GPI1: CBUS2->GPI1.2, RTS.2, U$19.10, U$23.P$1, X1.7
GPI2: CBUS4->GPI2.2, U$19.8, U$25.P$1, X1.5
GPI3: CBUS4->GPI1.2, U$51.8, U$57.P$1, X3.5
GPI4: CBUS2->GPI2.2, RTS1.2, U$51.10, U$55.P$1, X3.7
GPI5: CBUS4->GPI3.2, U$65.8, U$71.P$1, X5.5
GPI6: CBUS2->GPI3.2, RTS2.2, U$65.10, U$69.P$1, X5.7
GPI7: CBUS4->GPI4.2, U$79.8, U$85.P$1, X7.5
GPI8: CBUS2->GPI4.2, RTS3.2, U$79.10, U$83.P$1, X7.7
GPO1: CBUS0->GPO1.2, U$51.3, U$59.P$1, X3.1
GPO2: CBUS0->GPO2.2, U$19.3, U$27.P$1, X1.1
GPO3: CBUS0->GPO3.2, U$65.3, U$73.P$1, X5.1
GPO4: CBUS0->GPO4.2, U$79.3, U$87.P$1, X7.1
unnamed: U$2.6, V7805_C4.1
unnamed: IC1.32, RTS.1
unnamed: 12V_INPUT.1, D1.A
unnamed: CTS.1, IC1.8
unnamed: !SHDN!->GND.2, R1.1
unnamed: CBUS0->GPO2.1, IC1.22
unnamed: CBUS1->!SHDN!.1, IC1.21
unnamed: CBUS2->GPI1.1, IC1.10
unnamed: CBUS3->RSSI.1, IC1.11
unnamed: CBUS4->GPI2.1, IC1.9
unnamed: IC1.1, IC1.19, VCC_SELECT.2
unnamed: 3.3V_OUT.P$1, C5.2, IC1.16
unnamed: !RESET!.P$1, IC1.18
unnamed: U$33.6, V7805_C1.1
unnamed: 12V_INPUT1.1, D2.A
unnamed: IC6.32, RTS1.1
unnamed: CTS1.1, IC6.8
unnamed: !SHDN!->GND1.2, R2.1
unnamed: CBUS0->GPO1.1, IC6.22
unnamed: CBUS1->!SHDN!1.1, IC6.21
unnamed: CBUS2->GPI2.1, IC6.10
unnamed: CBUS3->RSSI1.1, IC6.11
unnamed: CBUS4->GPI1.1, IC6.9
unnamed: IC6.1, IC6.19, VCC_SELECT1.2
unnamed: 3.3V_OUT1.P$1, C11.2, IC6.16
unnamed: !RESET!1.P$1, IC6.18
unnamed: IC7.32, RTS2.1
unnamed: CTS2.1, IC7.8
unnamed: !SHDN!->GND2.2, R3.1
unnamed: CBUS0->GPO3.1, IC7.22
unnamed: CBUS1->!SHDN!2.1, IC7.21
unnamed: CBUS2->GPI3.1, IC7.10
unnamed: CBUS3->RSSI2.1, IC7.11
unnamed: CBUS4->GPI3.1, IC7.9
unnamed: IC7.1, IC7.19, VCC_SELECT2.2
unnamed: 3.3V_OUT2.P$1, C13.2, IC7.16
unnamed: !RESET!2.P$1, IC7.18
unnamed: IC8.32, RTS3.1
unnamed: CTS3.1, IC8.8
unnamed: !SHDN!->GND3.2, R4.1
unnamed: CBUS0->GPO4.1, IC8.22
unnamed: CBUS1->!SHDN!3.1, IC8.21
unnamed: CBUS2->GPI4.1, IC8.10
unnamed: CBUS3->RSSI3.1, IC8.11
unnamed: CBUS4->GPI4.1, IC8.9
unnamed: IC8.1, IC8.19, VCC_SELECT3.2
unnamed: 3.3V_OUT3.P$1, C15.2, IC8.16
unnamed: !RESET!3.P$1, IC8.18
RSSI: CBUS3->RSSI.2, U$19.11, U$22.P$1, X1.8
RSSI1: CBUS3->RSSI1.2, U$51.11, U$54.P$1, X3.8
RSSI2: CBUS3->RSSI2.2, U$65.11, U$68.P$1, X5.8
RSSI3: CBUS3->RSSI3.2, U$79.11, U$82.P$1, X7.8
RX: IC1.2, U$19.6, U$29.P$1, X1.3
RX1: IC6.2, U$51.6, U$61.P$1, X3.3
RX2: IC7.2, U$65.6, U$75.P$1, X5.3
RX3: IC8.2, U$79.6, U$89.P$1, X7.3
SHDN: !SHDN!->GND.1, CBUS1->!SHDN!.2, U$19.7, U$26.P$1, X1.4
SHDN1: !SHDN!->GND1.1, CBUS1->!SHDN!1.2, U$51.7, U$58.P$1, X3.4
SHDN2: !SHDN!->GND2.1, CBUS1->!SHDN!2.2, U$65.7, U$72.P$1, X5.4
SHDN3: !SHDN!->GND3.1, CBUS1->!SHDN!3.2, U$79.7, U$86.P$1, X7.4
TS7800_+: TS7800_CON.1, U$2.5, U$16.P$1, V7805_C6.1
TS7800_+1: TS7800_CON1.1, U$33.5, U$48.P$1, V7805_C3.1
TS7800_EN: S1.11, U$2.1, U$4.P$1, V7805_C5.1
TS7800_EN1: S2.11, U$33.1, U$36.P$1, V7805_C2.1
TX: IC1.30, U$19.5, U$28.P$1, X1.2
TX1: IC6.30, U$51.5, U$60.P$1, X3.2
TX2: IC7.30, U$65.5, U$74.P$1, X5.2
TX3: IC8.30, U$79.5, U$88.P$1, X7.2
TX_PWR: U$19.4, U$30.P$1
TX_PWR1: U$51.4, U$62.P$1
TX_PWR2: U$65.4, U$76.P$1
TX_PWR3: U$79.4, U$90.P$1
USBDM: IC1.15, U$31.P$1, X2.2
USBDM1: IC6.15, U$63.P$1, X4.2
USBDM2: IC7.15, U$77.P$1, X6.2
USBDM3: IC8.15, U$91.P$1, X8.2
USBDP: IC1.14, U$32.P$1, X2.3
USBDP1: IC6.14, U$64.P$1, X4.3
USBDP2: IC7.14, U$78.P$1, X6.3
USBDP3: IC8.14, U$92.P$1, X8.3
USB_VCC: C6.1, VCC_SELECT.1, X2.1
USB_VCC1: C12.1, VCC_SELECT1.1, X4.1
USB_VCC2: C14.1, VCC_SELECT2.1, X6.1
USB_VCC3: C16.1, VCC_SELECT3.1, X8.1
VCC: J1.1, U$19.2, U$21.P$1, VCC_SELECT.3
VCC1: J2.1, U$51.2, U$53.P$1, VCC_SELECT1.3
VCC2: J3.1, U$65.2, U$67.P$1, VCC_SELECT2.3
VCC3: J4.1, U$79.2, U$81.P$1, VCC_SELECT3.3
